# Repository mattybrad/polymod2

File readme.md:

# PolyMod 2

This is (or will be) an open source modular synthesizer, built using digital rather than analogue technology. This approach retains the flexibility of an analogue modular synth (e.g. Eurorack) while being cheaper to build. Other advantages include polyphony, a free open source database of modules to install, and the ability to save and retrieve patches.

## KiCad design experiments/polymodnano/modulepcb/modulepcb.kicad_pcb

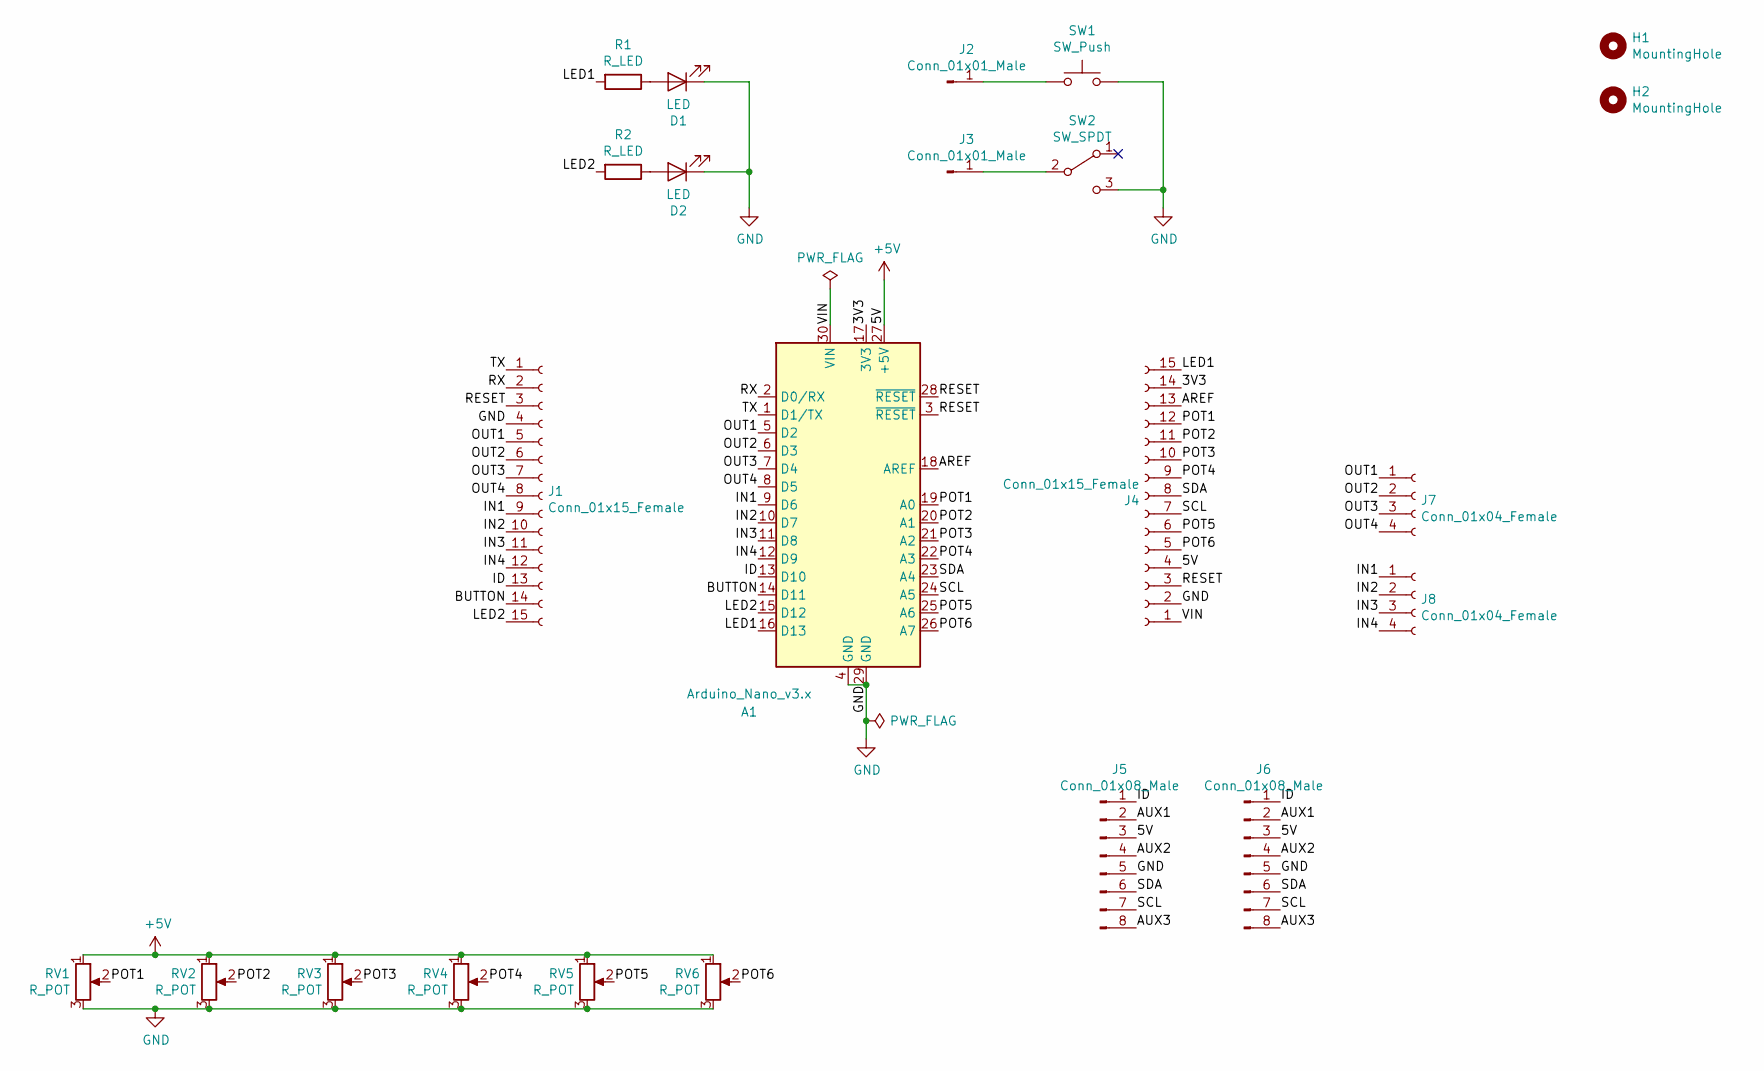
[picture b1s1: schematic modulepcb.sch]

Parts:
A1: Arduino_Nano_v3.x; Arduino_Nano
D1, D2: LED; LED_D5.0mm
H1, H2: MountingHole; MountingHole_3.2mm_M3
J1, J4: Conn_01x15_Female; PinHeader_1x15_P2.54mm_Vertical
J2, J3: Conn_01x01_Male; PinHeader_1x01_P2.54mm_Vertical
J5, J6: Conn_01x08_Male; PinHeader_1x08_P2.54mm_Vertical
J7, J8: Conn_01x04_Female; PinSocket_1x04_P2.54mm_Vertical
R1, R2: R_LED; R_Axial_DIN0204_L3.6mm_D1.6mm_P7.62mm_Horizontal
RV1, RV2, RV3, RV4, RV5, RV6: R_POT; Potentiometer_Alps_RK09K_Single_Vertical
SW1: SW_Push; SW_PUSH-12mm_Wuerth-430476085716
SW2: SW_SPDT; EG1206

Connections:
+5V: A1.27 (+5V), J4.4, J5.3, J6.3, RV1.1, RV2.1, RV3.1, RV4.1, RV5.1, RV6.1
/3V3: A1.17 (3V3), J4.14
/AREF: A1.18 (AREF), J4.13
/AUX1: J5.2, J6.2
/AUX2: J5.4, J6.4
/AUX3: J5.8, J6.8
/BUTTON: A1.14 (D11), J1.14
/ID: A1.13 (D10), J1.13, J5.1, J6.1
/IN1: A1.9 (D6), J1.9, J8.1
/IN2: A1.10 (D7), J1.10, J8.2
/IN3: A1.11 (D8), J1.11, J8.3
/IN4: A1.12 (D9), J1.12, J8.4
/LED1: A1.16 (D13), J4.15, R1.2
/LED2: A1.15 (D12), J1.15, R2.2
/OUT1: A1.5 (D2), J1.5, J7.1
/OUT2: A1.6 (D3), J1.6, J7.2
/OUT3: A1.7 (D4), J1.7, J7.3
/OUT4: A1.8 (D5), J1.8, J7.4
/POT1: A1.19 (A0), J4.12, RV1.2
/POT2: A1.20 (A1), J4.11, RV2.2
/POT3: A1.21 (A2), J4.10, RV3.2
/POT4: A1.22 (A3), J4.9, RV4.2
/POT5: A1.25 (A6), J4.6, RV5.2
/POT6: A1.26 (A7), J4.5, RV6.2
/RESET: A1.3 (~RESET), A1.28 (~RESET), J1.3, J4.3
/RX: A1.2 (D0/RX), J1.2
/SCL: A1.24 (A5), J4.7, J5.7, J6.7
/SDA: A1.23 (A4), J4.8, J5.6, J6.6
/TX: A1.1 (D1/TX), J1.1
/VIN: A1.30 (VIN), J4.1
GND: A1.4 (GND), A1.29 (GND), D1.1 (K), D2.1 (K), J1.4, J4.2, J5.5, J6.5, RV1.3, RV2.3, RV3.3, RV4.3, RV5.3, RV6.3, SW1.2, SW2.3 (C)
unnamed: D1.2 (A), R1.1
unnamed: D2.2 (A), R2.1
unnamed: J2.1, SW1.1
unnamed: J3.1, SW2.2 (B)

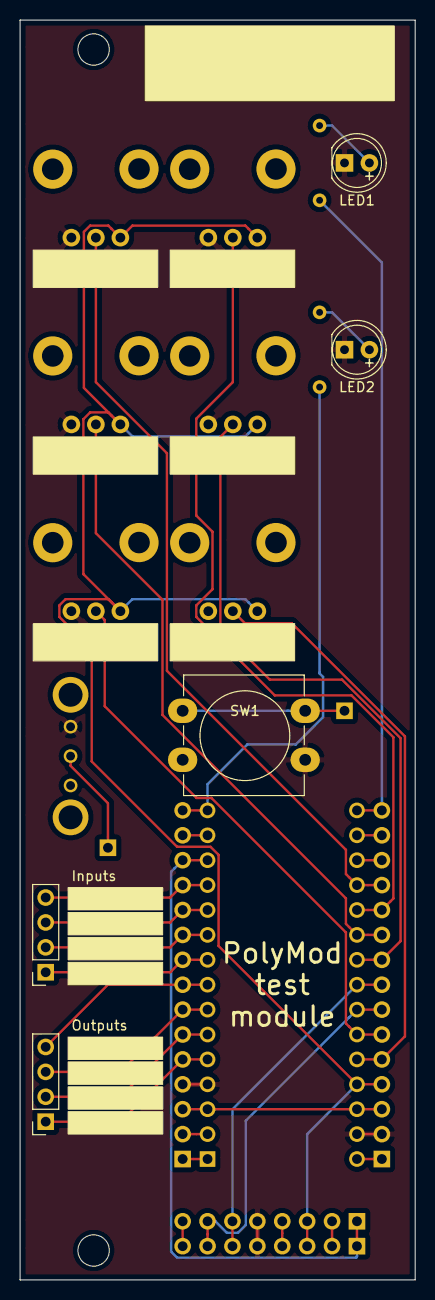
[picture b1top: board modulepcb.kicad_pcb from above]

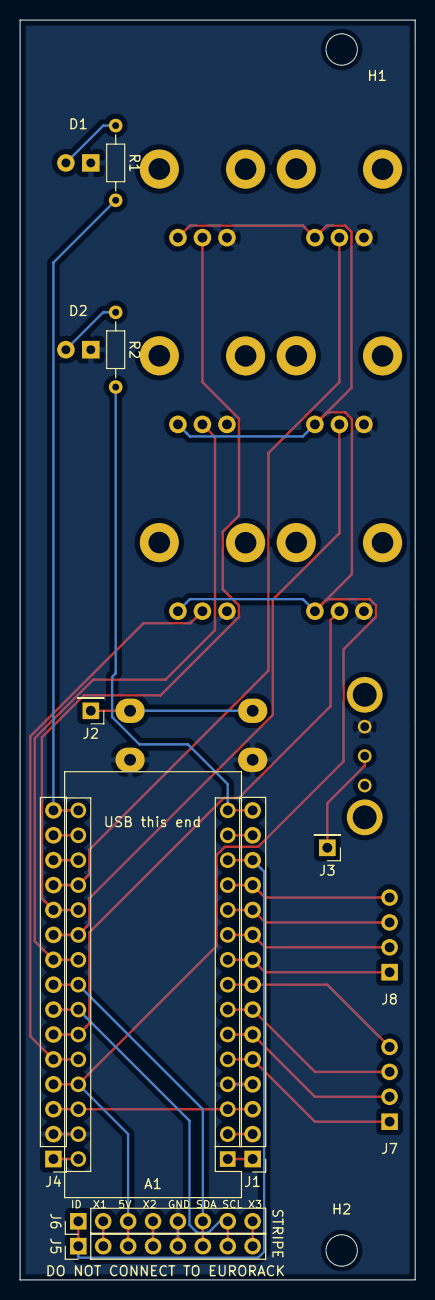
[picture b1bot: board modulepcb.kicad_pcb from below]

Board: 2 copper layers, 40.3 x 128.5 mm, 23 parts (9 on the bottom side), 35 nets.

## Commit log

2018-12-14 remembering how to do a node server
2018-12-14 more node and mongo from tutorial
2018-12-15 added module object to API
2018-12-15 API tweaks
2018-12-15 tidying up API
2018-12-15 added API read route
2018-12-16 all CRUD routes working
2018-12-16 new list route
2018-12-18 after much faffing, you can now sort of add synth module versions
2018-12-18 tidied up version post route
2018-12-18 simple html/jquery module list page
2018-12-18 clickable module links
2018-12-19 started the teensy code and began thinking about pin numbers
2018-12-21 laying out the code, figuring out the pins
2018-12-22 couple more planning comments, off home for xmas!
2018-12-23 added various empty classes and implemented basic menu system
2018-12-24 more messing about with menu system
2018-12-26 updated pseudo-code to support 64 modules rather than 8
2018-12-28 adding more code from previous version and new pseudo code, still just experimenting
2019-03-25 initial schematic design and fraught thoughts about pin allocation
2019-03-26 pins decided for now
2019-03-27 added some notes
2019-04-08 updated notes, changed pins
2019-04-09 added optimisation test sketch
2019-04-09 big speed boost from using ADC free-running mode
2019-04-16 played around with test sketches, lots of stuff now working, going to try and do the proper code
2019-04-16 receiving serial info into main sketch
2019-04-17 started the code proper
2019-04-17 physical patch cable detection working
2019-08-28 resurrecting the polymod 2 project - it kinda works!
2019-08-28 test setup fully working again
2019-08-28 how it works text file
2019-08-29 improved audio, layout, and click-to-start function
2019-08-29 loading dictionary text file
2019-08-29 oops
2019-08-30 still hacking around but breadboard patching working for now
2019-08-31 it compiles! making progress with the complex physical/virtual structure
2019-09-02 more progress, working through the boring stuff
2019-09-02 aha!! it wasn't working for ages because i was being stupid but then it worked
2019-09-02 tidying up, removing test code
2019-09-03 now trying to implement patch cables properly - getting there...
2019-09-03 ugh i hate pointers and references but it works again now
2019-09-03 actually working with real circuit patching!
2019-09-03 cable disconnection now works
2019-09-03 multiple outputs working on VCO module
2019-09-03 four waveforms in VCO module
2019-09-04 tried to get variable polyphony working and broke everything
2019-09-04 fixed silly mistake, polyphony values between 1 and 4 now work well
2019-09-04 can now have up to 8 notes polyphony, but memory usage starting to be a problem?
2019-09-04 added RAM monitoring code by Adrian Hunt
2019-09-04 experimenting with recursive function in javascript before trying in sketch
2019-09-04 recursive function looks good
2019-09-04 done messing about with javascript recursion function
2019-09-05 patch cables can now access any input or output in audiostreams, vco modulation working
2019-09-05 filter is working
2019-09-05 recursion.....
2020-03-25 oops haven't committed for ages
2020-03-25 Bump mongoose from 5.4.0 to 5.7.5 in /module_repo
    Bumps [mongoose](https://github.com/Automattic/mongoose) from 5.4.0 to 5.7.5.
    - [Release notes](https://github.com/Automattic/mongoose/releases)
    - [Changelog](https://github.com/Automattic/mongoose/blob/master/History.md)
    - [Commits](https://github.com/Automattic/mongoose/compare/5.4.0...5.7.5)
2020-03-25 oh dear, i'm definitely about to create a big merge conflict
2020-08-07 some pretty cool experiments brewing
2020-08-07 more cool stuff
2020-08-17 started module schematic
2020-08-17 First test for OSC and Python I2C communication with Arduino module
2020-08-17 Restore fakeserial.ino file
2020-08-18 created 8hp test module
2020-08-18 pcb done
2020-08-20 messing about with teensy code again
2020-08-20 teensy reading knobs
2020-08-21 more good teensy experiments
2020-08-27 i keep crashing the teensy
2020-08-27 js synth
2020-08-27 js synth makes some sounds
2020-08-28 js synth working ok
2020-08-28 checking mono/poly status works
2020-08-28 improvements to poly status calc
2020-08-28 better connect/disconnect function
2020-08-28 analog input object works
2020-08-28 can now destroy modules
2020-08-28 implemented volt per octave on oscillatornode
2020-08-28 still need to reduce gain before waveshaper
2020-08-29 attenuator before waveshaper
2020-08-30 added html module representation
2020-09-01 here comes a merge conflict...
2020-09-01 arduinos talking to chrome via midi
2020-09-02 moving inside
2020-09-02 module id system works really nicely
2020-09-03 made a mess but heading in right direction
2020-09-05 knobs working, leds working
2020-09-05 i broke things
2022-12-08 Bump qs and express in /experiments/js_synth
    Bumps [qs](https://github.com/ljharb/qs) to 6.11.0 and updates ancestor dependency [express](https://github.com/expressjs/express). These dependencies need to be updated together.
    Updates `qs` from 6.7.0 to 6.11.0
    - [Release notes](https://github.com/ljharb/qs/releases)
    - [Changelog](https://github.com/ljharb/qs/blob/main/CHANGELOG.md)
    - [Commits](https://github.com/ljharb/qs/compare/v6.7.0...v6.11.0)
    Updates `express` from 4.17.1 to 4.18.2
2022-12-08 Bump qs, body-parser and express in /module_repo
    Bumps [qs](https://github.com/ljharb/qs) to 6.11.0 and updates ancestor dependencies [qs](https://github.com/ljharb/qs), [body-parser](https://github.com/expressjs/body-parser) and [express](https://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
    Updates `qs` from 6.5.2 to 6.11.0
    - [Release notes](https://github.com/ljharb/qs/releases)
    - [Changelog](https://github.com/ljharb/qs/blob/main/CHANGELOG.md)
    - [Commits](https://github.com/ljharb/qs/compare/v6.5.2...v6.11.0)
    Updates `body-parser` from 1.18.3 to 1.20.1
2022-12-09 Bump express from 4.16.4 to 4.17.3 in /module_repo
    Bumps [express](https://github.com/expressjs/express) from 4.16.4 to 4.17.3.
    - [Release notes](https://github.com/expressjs/express/releases)
    - [Changelog](https://github.com/expressjs/express/blob/master/History.md)
    - [Commits](https://github.com/expressjs/express/compare/4.16.4...4.17.3)
    ---
    updated-dependencies:
2022-12-13 Bump express from 4.17.1 to 4.17.3 in /experiments/js_synth
    Bumps [express](https://github.com/expressjs/express) from 4.17.1 to 4.17.3.
    - [Release notes](https://github.com/expressjs/express/releases)
    - [Changelog](https://github.com/expressjs/express/blob/master/History.md)
    - [Commits](https://github.com/expressjs/express/compare/4.17.1...4.17.3)
    ---
    updated-dependencies:
2023-02-01 Bump mongoose from 5.7.5 to 5.13.15 in /module_repo
    Bumps [mongoose](https://github.com/Automattic/mongoose) from 5.7.5 to 5.13.15.
    - [Release notes](https://github.com/Automattic/mongoose/releases)
    - [Changelog](https://github.com/Automattic/mongoose/blob/master/CHANGELOG.md)
    - [Commits](https://github.com/Automattic/mongoose/compare/5.7.5...5.13.15)
    ---
    updated-dependencies:
